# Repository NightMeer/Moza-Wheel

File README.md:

# Moza Custom Wheel

A DIY solution to create custom steering wheels for Moza Wheelbases using an Arduino Pro Micro as an emulator.

## Disclaimer
> Modding your hardware can void your warranty. Use this project at your own risk. Be careful with the voltage settings on the step-down converter!
> **Crucial:** You must calibrate the step-down converter output voltage BEFORE connecting it to the Arduino to avoid permanent damage!
---
## Requirements
### Buy
- 4x [6.5mm Pogo Pins](https://de.aliexpress.com/item/1005008633095807.html)
- 1x [Arduino Pro Micro](https://de.aliexpress.com/item/1005009320469220.html) (5V/16MHz recommended)
- 1x [Stepdown](https://www.amazon.de/dp/B0CGVMRQXB)
- 1x [70mm Quick-Release](https://de.aliexpress.com/item/1005010038135486.html)
- 2x [M3 6mm](https://de.aliexpress.com/item/4000239264456.html) | PCB Pogo
- 6x [M3 Nut]() | Handle
- 6x [M3 25mm](https://de.aliexpress.com/item/4000239264456.html) | Handle
- 4x [M3 8mm](https://de.aliexpress.com/item/4000239264456.html) | Base
- 6x [M5 40mm](https://de.aliexpress.com/item/1005008846077891.html) | Wheel QR
- 12x [Button]()

### Print
- 1x Wheel Wheel Box
- 1x Wheel Wheel Base
- 1x Wheel Handle Left Bottom
- 1x Wheel Handle Right Bottom
- 1x Wheel Handle Left Top
- 1x Wheel Handle Right Top
- 1x Spacer Pi Stepdown
#### Option A: With custom PCB
- 1x Spacer PCB Spacer
#### Option B: With Printed "PCB"
- 1x Connector Pogo Pin 6.5mm
- 1x Connector Pogo Pin 6.5mm V2
- 1x Connector Pogo Pin 7mm

### Optional
- Connector PCB Orderd by JLCPCB
- Wheel Wheel Base Ordered by JLCCNC

### Software Requirements
- Arduino IDE
- [Code](Code/Code.ino)
---

## Documentation & Pinouts
- [Pro Micro Pinout](Documentation/Pinouts/Pro_Micro.md)
- [Base Pinout](Documentation/Pinouts/R9_V2.md)
- [Images](Documentation/Images)
- [Gerber Files Connector](Documentation/PCB/GERBER-Connector.zip)
- [Wiring Diagrams](Documentation/PCB)
- [3D Files](Documentation/3D)
- [Code](Code/Code.ino)

## Credits & Resources
- [Original Post](https://www.reddit.com/r/simracing/comments/1j4k9dj/reverse_engineered_moza_es_wheel/)
- [Github Link](https://github.com/MikeSzklarz/Arduino-Moza-Emulator)
- [More Images](https://imgur.com/a/arduino-moza-wheel-yghlPRm)
- [Original 3D Files](https://www.thingiverse.com/thing:4058270/files)
- [Base-3D Print Split](https://www.thingiverse.com/thing:4891321/files)

# Getting Started

1. **Print** all required files or order parts from a CNC/PCB service.
2. **Flash** `Code.ino` to the Arduino Pro Micro using the Arduino IDE.
3. **Step-down Calibration:** Connect the Step-down to the Wheelbase power pins (12V or 24V) and adjust the potentiometer until it outputs exactly **3.3V** (or 5V depending on your MCU/Setup). **Do this before connecting the Arduino!**
4. **Soldering:**
   - Solder the Pogo-Pin connector pins.
   - Connect the calibrated Step-down output to the Arduino (VCC/GND).
   - Solder SDA & SCL lines from the base to the Arduino (Pins 2 & 3).
   - Solder your Buttons and Shifters to the Arduino pins.
5. **Final Assembly:** Mount all components into the wheel box and screw everything together.
6. **Connection:** Connect your wheel to the Moza Base and check for recognition in Moza Pit House.

# Further Information
- **LED/Input Logic:** In this setup, I used the pins to read a **HIGH** signal for the buttons.
- **Manufacturing:** For a more rigid feel, I highly recommend ordering the Base and the Connector PCB from JLC (CNC/PCB).

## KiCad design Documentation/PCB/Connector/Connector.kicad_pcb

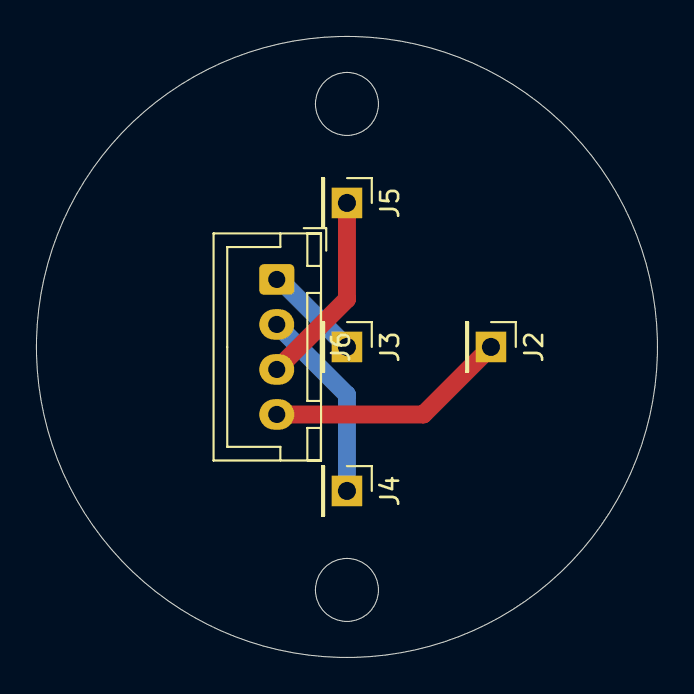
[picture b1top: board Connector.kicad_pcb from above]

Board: 2 copper layers, 34.5 x 34.5 mm, 7 parts (0 on the bottom side), 4 nets.

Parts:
H1, H2: MountingHole; MountingHole_3.5mm
J2, J3, J4, J5: Conn_01x01_Pin; PinHeader_1x01_P2.54mm_Vertical
J6: Conn_01x04; JST_XH_B4B-XH-A_1x04_P2.50mm_Vertical

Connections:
GND: J3.1, J6.1
SCL: J4.1, J6.2
SDA: J5.1, J6.3
VCC: J2.1, J6.4

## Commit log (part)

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2026-01-04 add Pro-Micro and Base Pinout
2026-01-04 Update "Documentation"
2026-01-04 Add Links
2026-01-21 Update Bom
